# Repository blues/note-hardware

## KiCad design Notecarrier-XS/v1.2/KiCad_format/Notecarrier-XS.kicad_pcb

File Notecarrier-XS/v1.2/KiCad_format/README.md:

# Notecarrier-XS — KiCad format

This directory contains the design files for the Blues **Notecarrier-XS**
in **KiCad 9** format, ported from the internal Altium Designer sources
(project `100426_notecarrier-xs`, Byte Lab Grupa d.o.o. for Blues) and
validated against the shipped production BOM and the published v1.2
fabrication package — see
[`documentation/Porting-Notes.md`](documentation/Porting-Notes.md) and
[`validation/`](validation/).

> **⚠️ Disclaimer:** the exact Altium snapshot that produced the published
> v1.2 fabrication package was never captured in version control, so this
> port was made from the closest available source — the post-v1.2
> development state. It differs from the published v1.2 board in two
> reviewed, documented ways: the silkscreen reads **V1.3** (with legend text
> repositioned), and **R4** — a production-DNP 0R jumper for the optional
> GPS-power path — sits on the opposite board side. Copper, mask, paste and
> drill are otherwise exact against the published fab package, and the
> netlist matches the source design 57/57. Details in
> [`documentation/Porting-Notes.md`](documentation/Porting-Notes.md).
>
> Since publication the port has additionally been checked against the
> **released build's** pick-and-place file: all 44 placed parts match the
> shipped boards on side and rotation.
>
> The design house's October 2026 "Rev-11" snapshot turned out to be the
> **v1.1** board, not v1.2, so this disclaimer remains (the Notecarrier-X and
> -XM ports were regenerated from their Rev-11 snapshots and no longer carry
> one). See the Porting-Notes update.

## Contents

| Path | Description |
|---|---|
| `Notecarrier-XS.kicad_pro` / `.kicad_prl` | KiCad project |
| `Notecarrier-XS.kicad_sch` | Root schematic sheet |
| `Notecarrier-XS_IO-Connection.kicad_sch` | IO connection sheet |
| `Notecarrier-XS_Notecard-Connection.kicad_sch` | Notecard connection sheet |
| `Notecarrier-XS_Power.kicad_sch` | Power sheet |
| `Notecarrier-XS_Starnote-Connection.kicad_sch` | Starnote connection sheet |
| `Notecarrier-XS.kicad_pcb` | 2-layer board (zone fills preserved from the Altium import — do not refill) |
| `Notecarrier-XS.kicad_wks` | Drawing sheet (shared Blues template) |
| `Notecarrier-XS-altium-import.kicad_sym` / `.pretty/` | Project libraries captured during the import |
| `sym-lib-table` / `fp-lib-table` | Library tables |
| `documentation/` | Porting notes (incl. the source-fidelity disclaimer) and plotted PDFs |
| `manufacturing/Notecarrier-XS_RevA.zip` | KiCad-exported gerbers + drill |
| `validation/` | Validation-gate artifacts (ERC/DRC/BOM reports, per-layer gerber diffs, kicanvas renders) |

The schematic references the shared Blues symbol/footprint library via the
`BLUES_KICAD_LIB_DIR` path variable
([blues-kicad-lib](https://github.com/blues/blues-kicad-lib)), with all
symbols and footprints used by this design also embedded in the project
libraries above, so the project opens standalone.

## Provenance

Ported from Altium Designer sources with KiCad 9.0.9's importer and the
validation harness in
[`_Tools/kicad_validation/`](../../../_Tools/kicad_validation/). The original
Altium sources are internal and are not part of this repository; the
published v1.2 fabrication package (`../2200-914__2024-06-06.zip`), BOM
(`../BOM-3000-789-002.xlsx`) and drawings in the parent folder remain the
manufacturing ground truth for the shipped product.

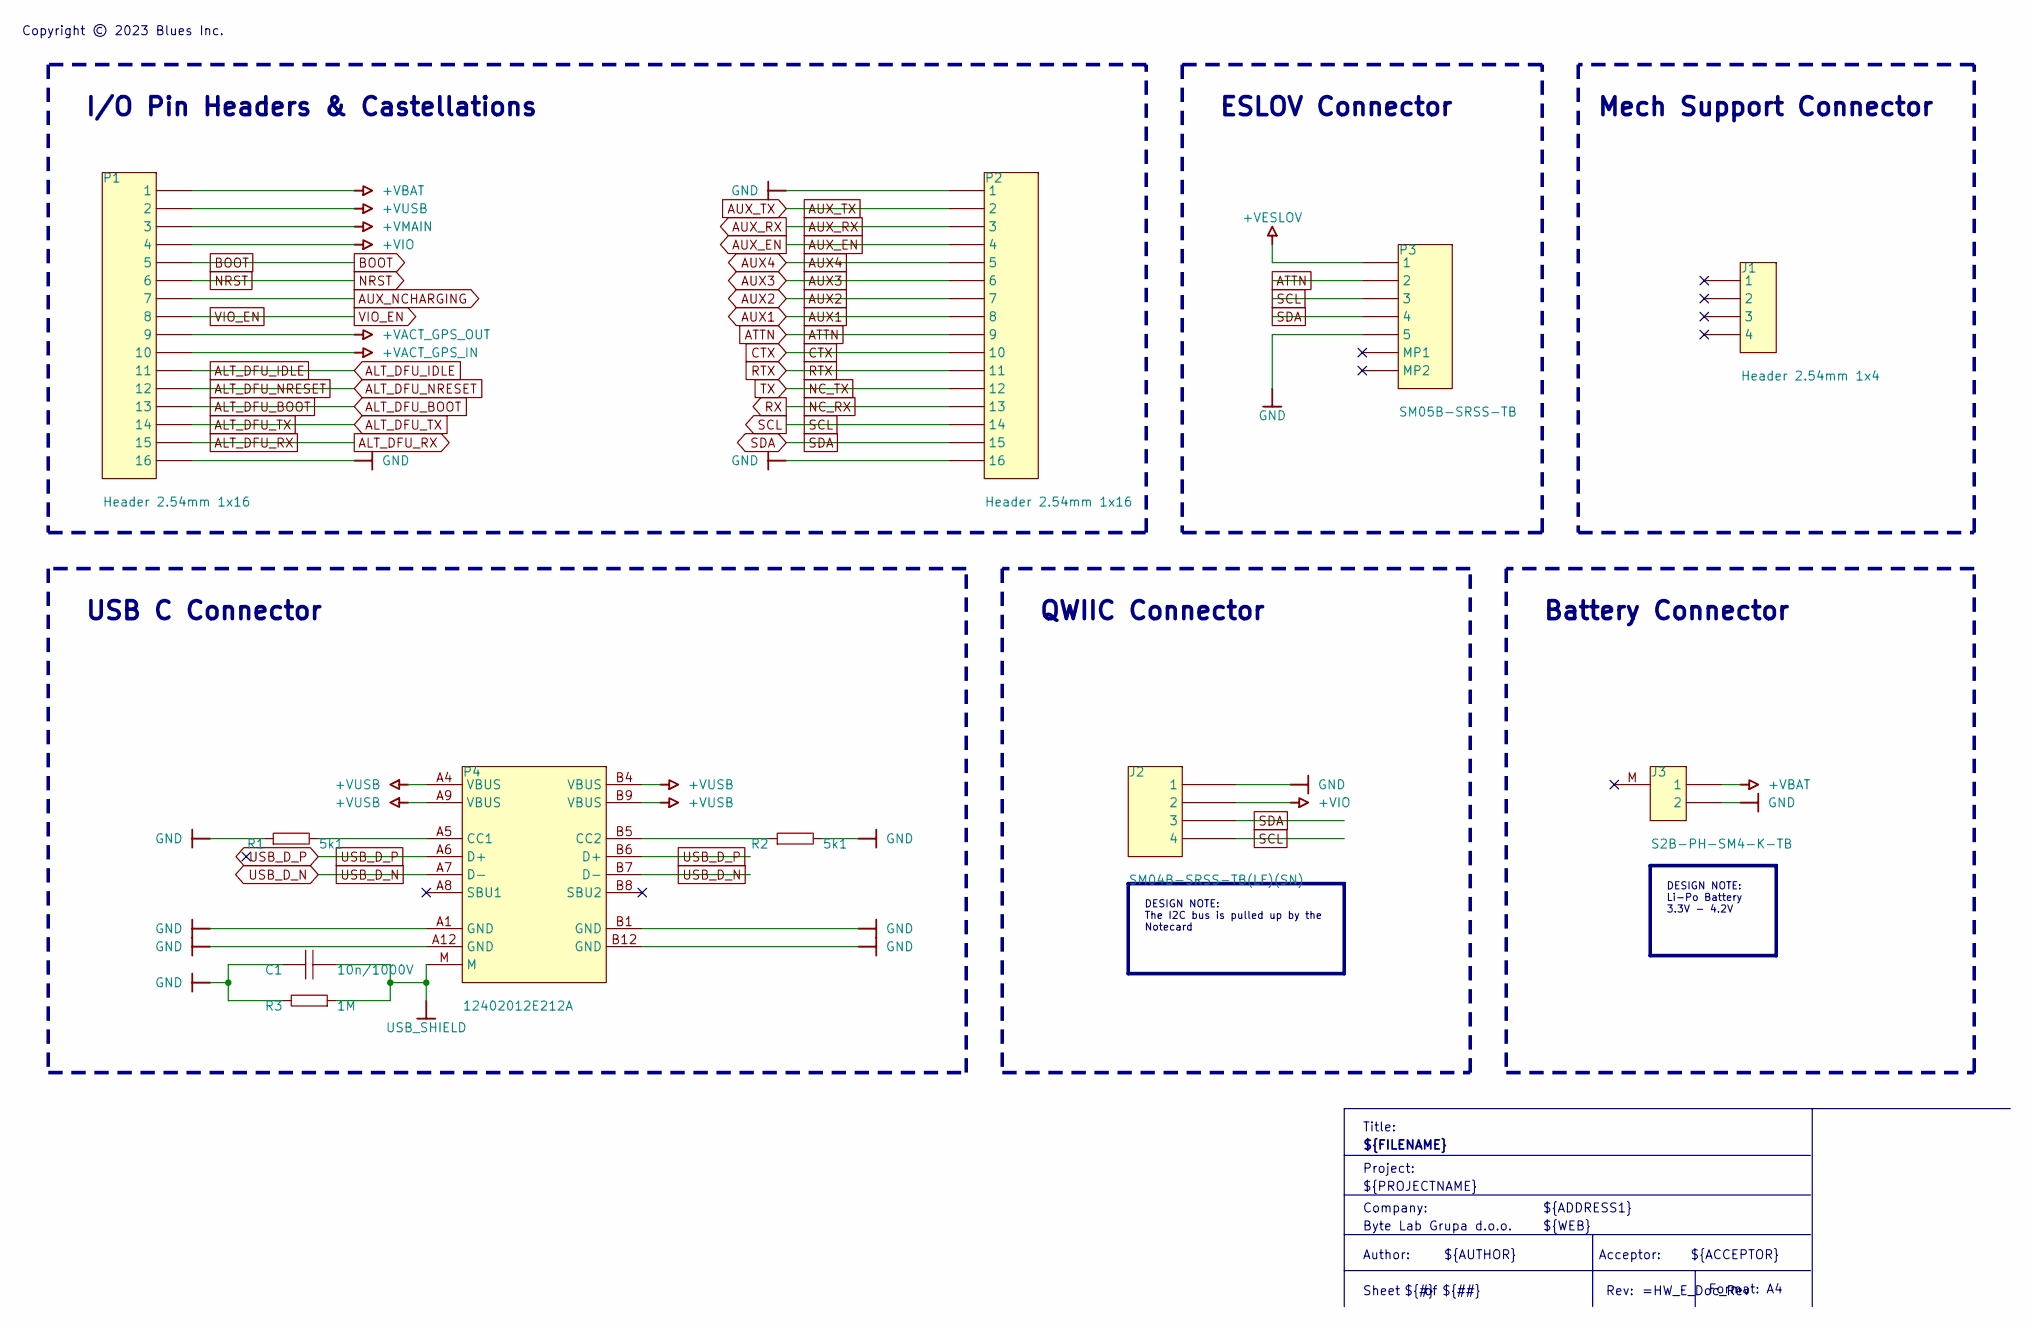
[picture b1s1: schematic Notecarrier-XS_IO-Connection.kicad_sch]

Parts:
C1: 10n/1000V; C-1206; MANUFACTURER PART NUMBER CS1206KKX7RCBB103
J1: Header 2.54mm 1x4; Header 2.54mm 1X4; MANUFACTURER PART NUMBER N/A
J2: SM04B-SRSS-TB(LF)(SN); JST SM04B-SRSS-TB; MANUFACTURER PART NUMBER SM04B-SRSS-TB(LF)(SN)
J3: S2B-PH-SM4-K-TB; Conn S2B-PH-SM4; MANUFACTURER PART NUMBER S2B-PH-SM4-K-TB(LF)(SN)
P1, P2: Header 2.54mm 1x16; Header 2.54mm 1X16; MANUFACTURER PART NUMBER N/A
P3: SM05B-SRSS-TB; Conn_SM05B-SRSS-TB; MANUFACTURER PART NUMBER SM05B-SRSS-TB
P4: 12402012E212A; CONN_12402012E212A; MANUFACTURER PART NUMBER 12402012E212A
R1, R2: 5k1; R-0402; MANUFACTURER PART NUMBER N/A
R3: 1M; R-1206; MANUFACTURER PART NUMBER N/A

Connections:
+VACT_GPS_IN: P1.10; also elsewhere on the board
+VACT_GPS_OUT: P1.9; also elsewhere on the board
+VBAT: J3.1, P1.1; also elsewhere on the board
+VESLOV: P3.1; also elsewhere on the board
+VIO: J2.2, P1.4; also elsewhere on the board
+VMAIN: P1.3; also elsewhere on the board
+VUSB: P1.2, P4.A4 (VBUS), P4.A9 (VBUS), P4.B4 (VBUS), P4.B9 (VBUS); also elsewhere on the board
ALT_DFU_BOOT: P1.13; also elsewhere on the board
ALT_DFU_IDLE: P1.11; also elsewhere on the board
ALT_DFU_NRESET: P1.12; also elsewhere on the board
ALT_DFU_RX: P1.15; also elsewhere on the board
ALT_DFU_TX: P1.14; also elsewhere on the board
ATTN: P2.9, P3.2; also elsewhere on the board
AUX1: P2.8; also elsewhere on the board
AUX2: P2.7; also elsewhere on the board
AUX3: P2.6; also elsewhere on the board
AUX4: P2.5; also elsewhere on the board
AUX_EN: P2.4; also elsewhere on the board
AUX_NCHARGING: P1.7; also elsewhere on the board
AUX_RX: P2.3; also elsewhere on the board
AUX_TX: P2.2; also elsewhere on the board
BOOT: P1.5; also elsewhere on the board
CTX: P2.10; also elsewhere on the board
GND: C1.2, J2.1, J3.2, P1.16, P2.1, P2.16, P3.5, P4.A1 (GND), P4.A12 (GND), P4.B1 (GND), P4.B12 (GND), R1.1, R2.2, R3.2; also elsewhere on the board
NC_RX: P2.13; also elsewhere on the board
NC_TX: P2.12; also elsewhere on the board
NRST: P1.6; also elsewhere on the board
unnamed: P4.A5 (CC1), R1.2
unnamed: P4.B5 (CC2), R2.1
RTX: P2.11; also elsewhere on the board
SCL: J2.4, P2.14, P3.3; also elsewhere on the board
SDA: J2.3, P2.15, P3.4; also elsewhere on the board
USB_D_N: P4.A7 (D-), P4.B7 (D-); also elsewhere on the board
USB_D_P: P4.A6 (D+), P4.B6 (D+); also elsewhere on the board
USB_SHIELD: C1.1, P4.M, R3.1
VIO_EN: P1.8; also elsewhere on the board

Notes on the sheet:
ESLOV Connector
${ACCEPTOR}
QWIIC Connector
Title:
Rev:
Sheet
Format: A4
Author:
I/O Pin Headers & Castellations
${ADDRESS1}
Acceptor:
${##}
${FILENAME}
Mech Support Connector
Company:
${REVISION}
${WEB}
${COMPANY}
Copyright © 2023 Blues Inc.
Battery Connector
USB C Connector
${#}
${AUTHOR}
${PROJECTNAME}
Project:
DESIGN NOTE: Li-Po Battery 3.3V - 4.2V
DESIGN NOTE: The I2C bus is pulled up by the Notecard

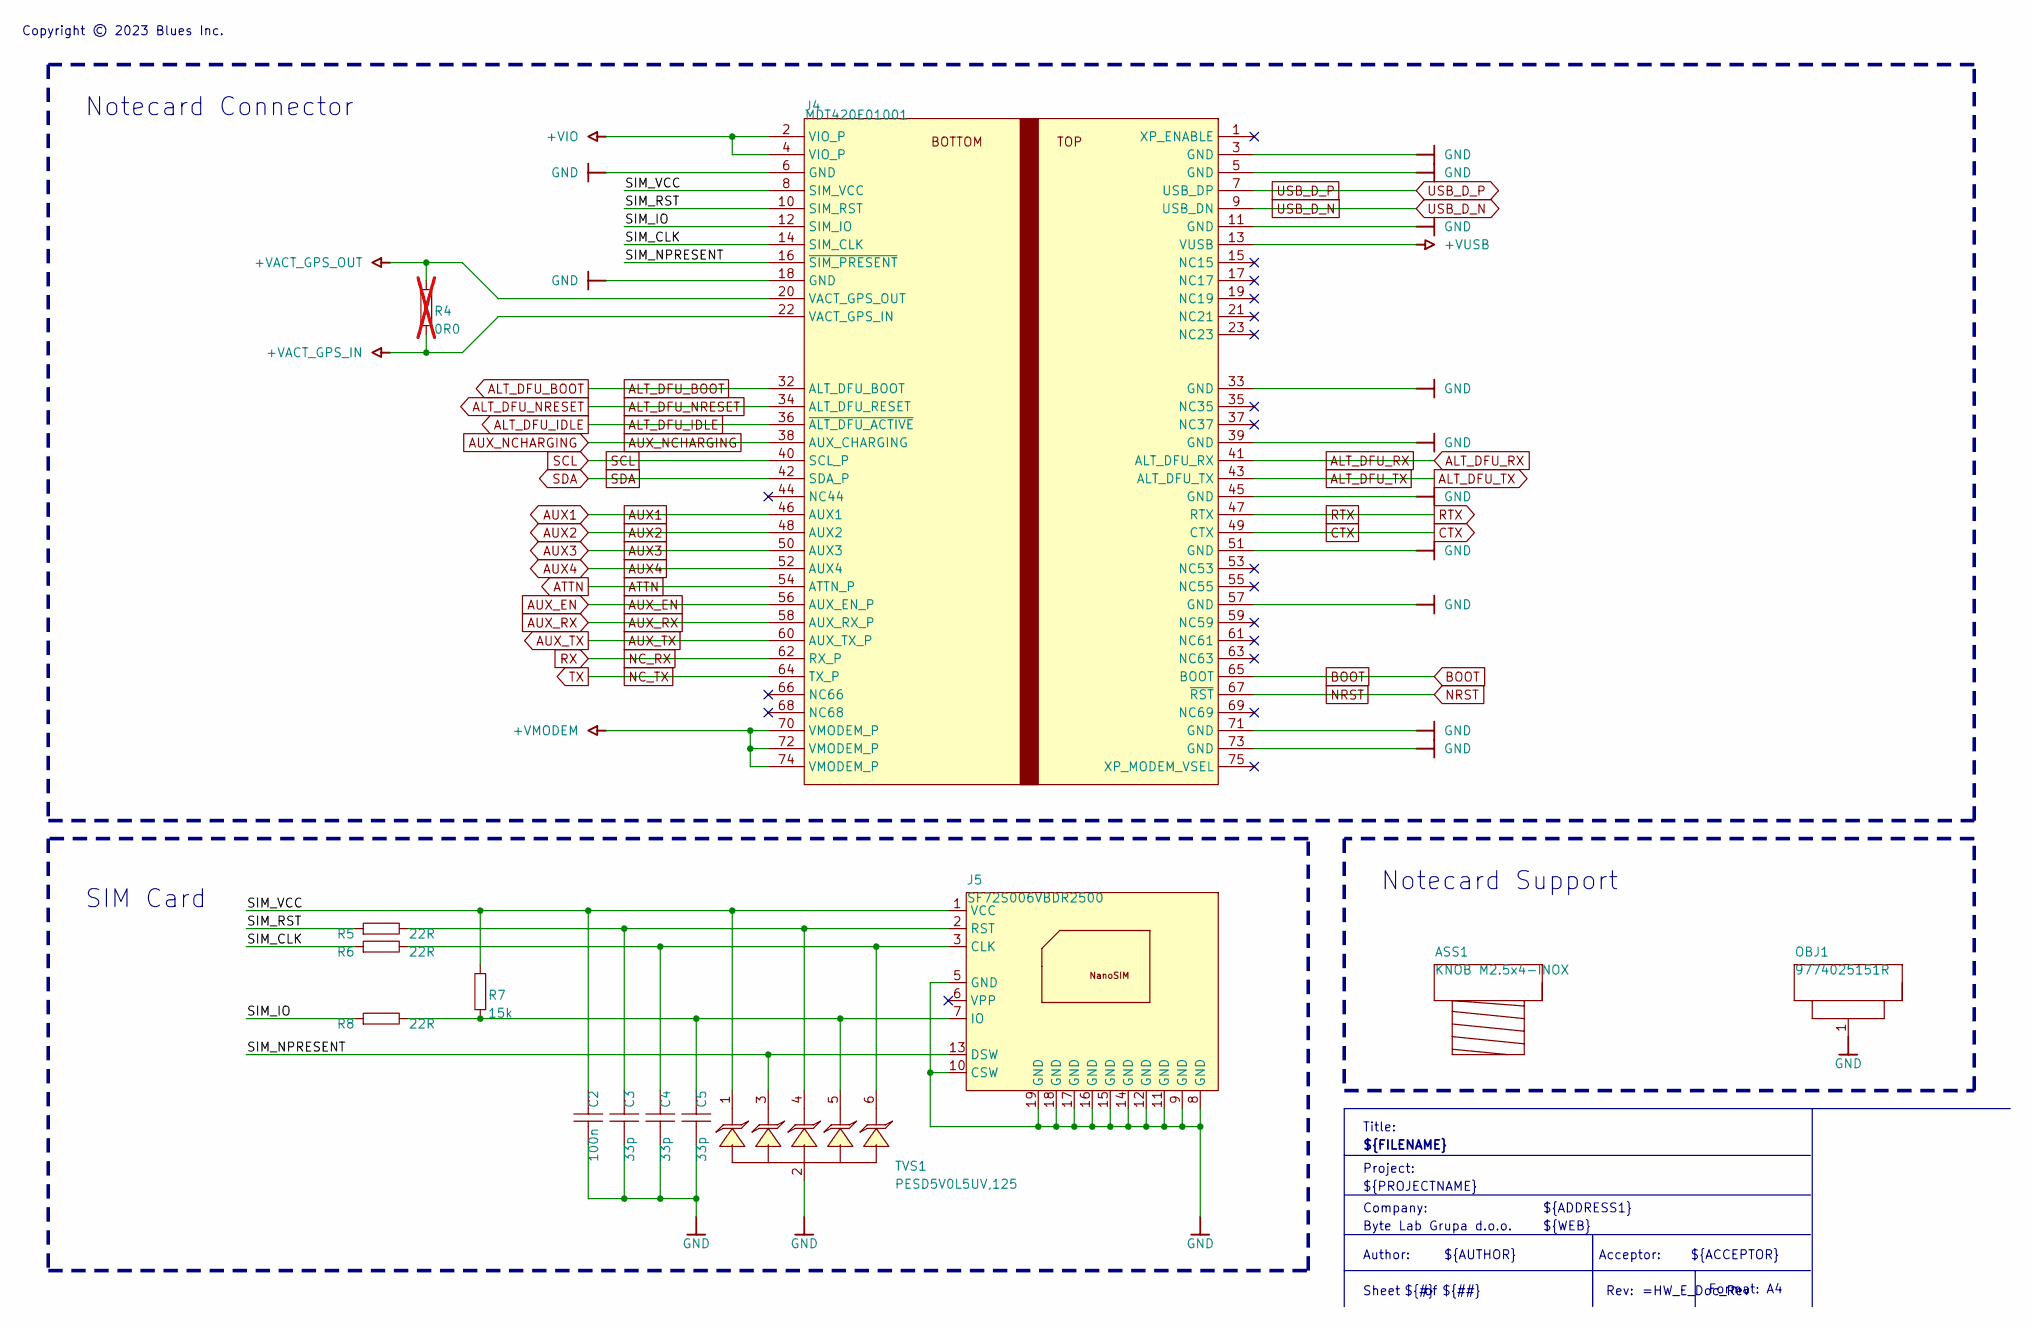
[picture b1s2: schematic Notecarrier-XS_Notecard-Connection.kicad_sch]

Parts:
ASS1: KNOB M2.5x4-INOX; MANUFACTURER PART NUMBER M2.5X4/D7985-A2
C2: 100n; C-0402; MANUFACTURER PART NUMBER N/A
C3, C4, C5: 33p; C-0402; MANUFACTURER PART NUMBER N/A
J4: MDT420E01001; J-75-0050-MOS-M2; MANUFACTURER PART NUMBER MDT420E03001
J5: SF72S006VBDR2500; J-NANOSIM-SF72S006VBA; MANUFACTURER PART NUMBER SF72S006VBDR2500
OBJ1: 9774025151R; DIST-WASMSIM0250; MANUFACTURER PART NUMBER 9774025151R
R4: 0R0; R-0603; MANUFACTURER PART NUMBER N/A; not fitted
R5, R6, R8: 22R; R-0402; MANUFACTURER PART NUMBER N/A
R7: 15k; R-0402; MANUFACTURER PART NUMBER N/A
TVS1: PESD5V0L5UV,125; SOT666; MANUFACTURER PART NUMBER PESD5V0L5UV,125

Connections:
+VACT_GPS_IN: J4.22 (VACT_GPS_IN), R4.1; also elsewhere on the board
+VACT_GPS_OUT: J4.20 (VACT_GPS_OUT), R4.2; also elsewhere on the board
+VIO: J4.2 (VIO_P), J4.4 (VIO_P); also elsewhere on the board
+VMODEM: J4.70 (VMODEM_P), J4.72 (VMODEM_P), J4.74 (VMODEM_P); also elsewhere on the board
+VUSB: J4.13 (VUSB); also elsewhere on the board
/Notecard Connection/SIM_CLK: J4.14 (SIM_CLK), R6.1
/Notecard Connection/SIM_IO: J4.12 (SIM_IO), R8.1
/Notecard Connection/SIM_NPRESENT: J4.16 (~SIM_PRESENT), J5.13 (DSW), TVS1.3 (C3)
/Notecard Connection/SIM_RST: J4.10 (SIM_RST), R5.1
/Notecard Connection/SIM_VCC: C2.2, J4.8 (SIM_VCC), J5.1 (VCC), R7.2, TVS1.1 (C1)
ALT_DFU_BOOT: J4.32 (ALT_DFU_BOOT); also elsewhere on the board
ALT_DFU_IDLE: J4.36 (~ALT_DFU_ACTIVE); also elsewhere on the board
ALT_DFU_NRESET: J4.34 (ALT_DFU_RESET); also elsewhere on the board
ALT_DFU_RX: J4.41 (ALT_DFU_RX); also elsewhere on the board
ALT_DFU_TX: J4.43 (ALT_DFU_TX); also elsewhere on the board
ATTN: J4.54 (ATTN_P); also elsewhere on the board
AUX1: J4.46 (AUX1); also elsewhere on the board
AUX2: J4.48 (AUX2); also elsewhere on the board
AUX3: J4.50 (AUX3); also elsewhere on the board
AUX4: J4.52 (AUX4); also elsewhere on the board
AUX_EN: J4.56 (AUX_EN_P); also elsewhere on the board
AUX_NCHARGING: J4.38 (AUX_CHARGING); also elsewhere on the board
AUX_RX: J4.58 (AUX_RX_P); also elsewhere on the board
AUX_TX: J4.60 (AUX_TX_P); also elsewhere on the board
BOOT: J4.65 (BOOT); also elsewhere on the board
CTX: J4.49 (CTX); also elsewhere on the board
GND: C2.1, C3.1, C4.1, C5.1, J4.3 (GND), J4.5 (GND), J4.6 (GND), J4.11 (GND), J4.18 (GND), J4.33 (GND), J4.39 (GND), J4.45 (GND), J4.51 (GND), J4.57 (GND), J4.71 (GND), J4.73 (GND), J5.5 (GND), J5.8 (GND), J5.9 (GND), J5.10 (CSW), J5.11 (GND), J5.12 (GND), J5.14 (GND), J5.15 (GND), J5.16 (GND), J5.17 (GND), J5.18 (GND), J5.19 (GND), OBJ1.1, TVS1.2 (A2); also elsewhere on the board
NC_RX: J4.62 (RX_P); also elsewhere on the board
NC_TX: J4.64 (TX_P); also elsewhere on the board
NRST: J4.67 (~RST); also elsewhere on the board
unnamed: C4.2, J5.3 (CLK), R6.2, TVS1.6 (C6)
unnamed: C5.2, J5.7 (IO), R7.1, R8.2, TVS1.5 (A5)
unnamed: C3.2, J5.2 (RST), R5.2, TVS1.4 (C4)
RTX: J4.47 (RTX); also elsewhere on the board
SCL: J4.40 (SCL_P); also elsewhere on the board
SDA: J4.42 (SDA_P); also elsewhere on the board
USB_D_N: J4.9 (USB_DN); also elsewhere on the board
USB_D_P: J4.7 (USB_DP); also elsewhere on the board

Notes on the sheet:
Notecard Connector
${ADDRESS1}
Rev:
Company:
Format: A4
${WEB}
Copyright © 2023 Blues Inc.
Author:
${##}
Sheet
Title:
Project:
${COMPANY}
Acceptor:
${ACCEPTOR}
${FILENAME}
${#}
Notecard Support
${REVISION}
${PROJECTNAME}
SIM Card
${AUTHOR}

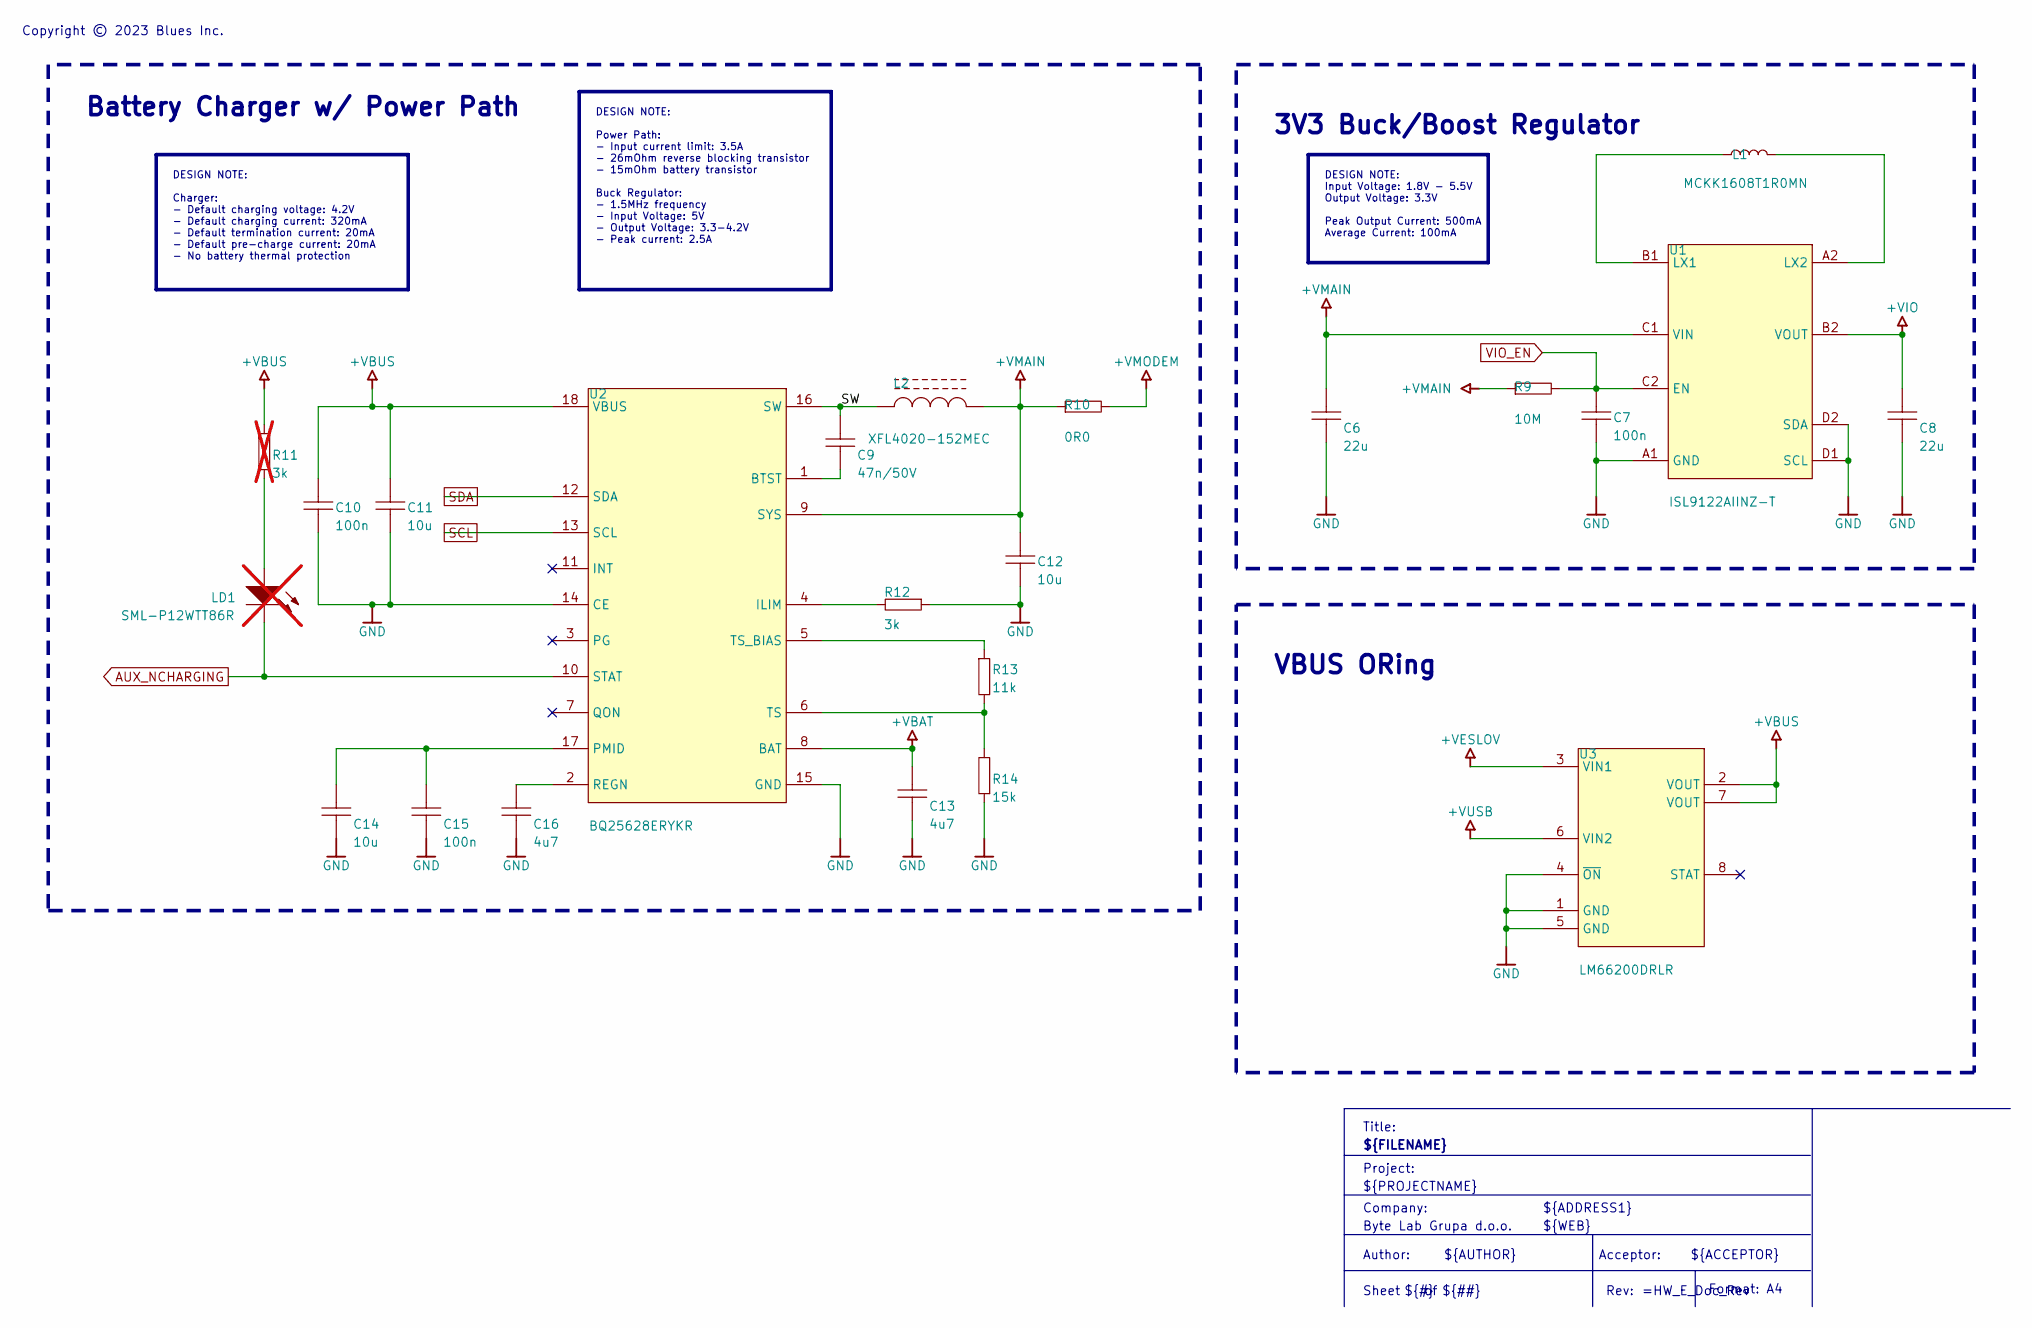
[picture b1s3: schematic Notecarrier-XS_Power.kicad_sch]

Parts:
C6, C8: 22u; C-0805; MANUFACTURER PART NUMBER N/A
C7, C10, C15: 100n; C-0402; MANUFACTURER PART NUMBER N/A
C9: 47n/50V; C-0402; MANUFACTURER PART NUMBER N/A
C11, C12: 10u; C-1206; MANUFACTURER PART NUMBER N/A
C13, C16: 4u7; C-0603; MANUFACTURER PART NUMBER N/A
C14: 10u; C-0805; MANUFACTURER PART NUMBER GRM21BR61E106MA73L
L1: MCKK1608T1R0MN; L-0603; MANUFACTURER PART NUMBER MCKK1608T1R0MN
L2: XFL4020-152MEC; IND_XFL4020; MANUFACTURER PART NUMBER XFL4020-152MEC
LD1: SML-P12WTT86R; LED-0402; MANUFACTURER PART NUMBER SML-P12WTT86R; not fitted
R9: 10M; R-0402; MANUFACTURER PART NUMBER N/A
R10: 0R0; R-0603; MANUFACTURER PART NUMBER N/A
R11: 3k; R-0402; MANUFACTURER PART NUMBER N/A; not fitted
R12: 3k; R-0402; MANUFACTURER PART NUMBER N/A
R13: 11k; R-0402; MANUFACTURER PART NUMBER N/A
R14: 15k; R-0402; MANUFACTURER PART NUMBER N/A
U1: ISL9122AIINZ-T; BGA8N40P2X4_180x100x50; MANUFACTURER PART NUMBER ISL9122AIINZ-T
U2: BQ25628ERYKR; QFN40P300X150X80-18N; MANUFACTURER PART NUMBER BQ25628ERYKR
U3: LM66200DRLR; SOT-583; MANUFACTURER PART NUMBER LM66200DRLR

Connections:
+VBAT: C13.2, U2.8 (BAT); also elsewhere on the board
+VBUS: C10.1, C11.1, R11.2, U2.18 (VBUS), U3.2 (VOUT), U3.7 (VOUT)
+VESLOV: U3.3 (VIN1); also elsewhere on the board
+VIO: C8.2, U1.B2 (VOUT); also elsewhere on the board
+VMAIN: C6.2, C12.1, L2.2, R9.1, R10.1, U1.C1 (VIN), U2.9 (SYS); also elsewhere on the board
+VMODEM: R10.2; also elsewhere on the board
+VUSB: U3.6 (VIN2); also elsewhere on the board
/Power/SW: C9.2, L2.1, U2.16 (SW)
AUX_NCHARGING: LD1.2 (K), U2.10 (STAT); also elsewhere on the board
GND: C6.1, C7.2, C8.1, C10.2, C11.2, C12.2, C13.1, C14.1, C15.1, C16.1, R12.1, R14.1, U1.A1 (GND), U1.D1 (SCL), U1.D2 (SDA), U2.14 (CE), U2.15 (GND), U3.1 (GND), U3.4 (~ON), U3.5 (GND); also elsewhere on the board
unnamed: LD1.1 (A), R11.1
unnamed: L1.1, U1.B1 (LX1)
unnamed: L1.2, U1.A2 (LX2)
unnamed: C9.1, U2.1 (BTST)
unnamed: R12.2, U2.4 (ILIM)
unnamed: C14.2, C15.2, U2.17 (PMID)
unnamed: C16.2, U2.2 (REGN)
unnamed: R13.2, R14.2, U2.6 (TS)
unnamed: R13.1, U2.5 (TS_BIAS)
SCL: U2.13 (SCL); also elsewhere on the board
SDA: U2.12 (SDA); also elsewhere on the board
VIO_EN: C7.1, R9.2, U1.C2 (EN); also elsewhere on the board

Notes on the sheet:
Copyright © 2023 Blues Inc.
Company:
${ADDRESS1}
${REVISION}
Acceptor:
Rev:
${##}
${PROJECTNAME}
${#}
Format: A4
Project:
${COMPANY}
${ACCEPTOR}
${WEB}
${FILENAME}
Sheet
VBUS ORing
3V3 Buck/Boost Regulator
Battery Charger w/ Power Path
Author:
${AUTHOR}
Title:
DESIGN NOTE: Input Voltage: 1.8V - 5.5V Output Voltage: 3.3V Peak Output Current: 500mA Average Current: 100mA
DESIGN NOTE: Charger: - Default charging voltage: 4.2V - Default charging current: 320mA - Default termination current: 20mA - Default pre-charge current: 20mA - No battery thermal protection
DESIGN NOTE: Power Path: - Input current limit: 3.5A - 26mOhm reverse blocking transistor - 15mOhm battery transistor Buck Regulator: - 1.5MHz frequency - Input Voltage: 5V - Output Voltage: 3.3-4.2V - Peak current: 2.5A

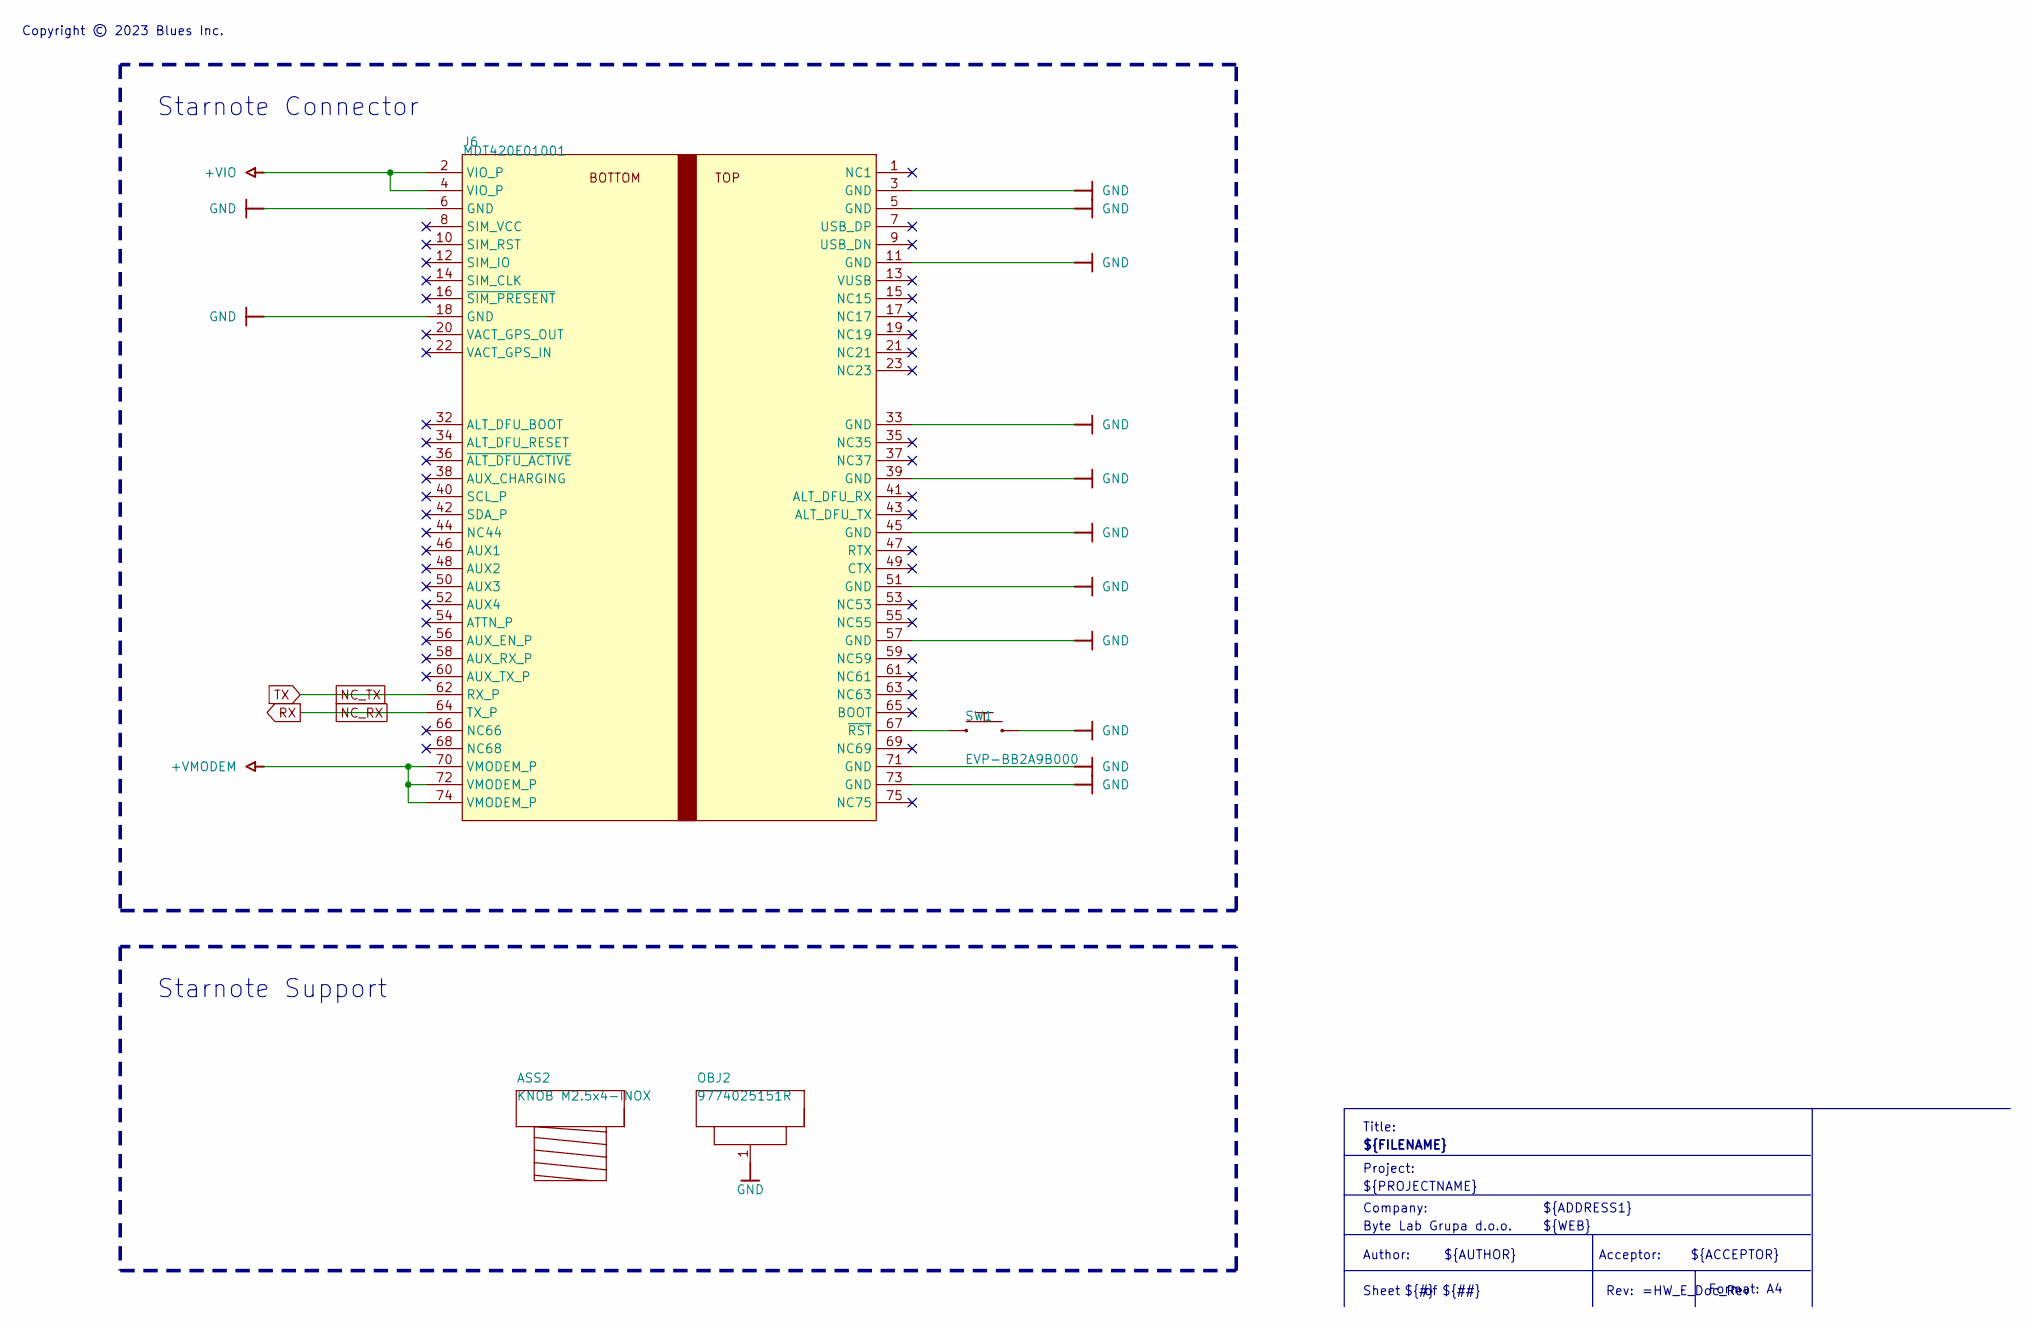
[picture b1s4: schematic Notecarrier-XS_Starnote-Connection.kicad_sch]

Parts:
ASS2: KNOB M2.5x4-INOX; MANUFACTURER PART NUMBER M2.5X4/D7985-A2
J6: MDT420E01001; J-75-0050-MOS-M2; MANUFACTURER PART NUMBER MDT420E03001
OBJ2: 9774025151R; DIST-WASMSIM0250; MANUFACTURER PART NUMBER 9774025151R
SW1: EVP-BB2A9B000; SW_EVP-BB2A9B000; MANUFACTURER PART NUMBER EVP-BB2A9B000

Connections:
+VIO: J6.2 (VIO_P), J6.4 (VIO_P); also elsewhere on the board
+VMODEM: J6.70 (VMODEM_P), J6.72 (VMODEM_P), J6.74 (VMODEM_P); also elsewhere on the board
GND: J6.3 (GND), J6.5 (GND), J6.6 (GND), J6.11 (GND), J6.18 (GND), J6.33 (GND), J6.39 (GND), J6.45 (GND), J6.51 (GND), J6.57 (GND), J6.71 (GND), J6.73 (GND), OBJ2.1, SW1.2 (B); also elsewhere on the board
NC_RX: J6.64 (TX_P); also elsewhere on the board
NC_TX: J6.62 (RX_P); also elsewhere on the board
unnamed: J6.67 (~RST), SW1.1 (A)

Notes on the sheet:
${COMPANY}
Rev:
${AUTHOR}
Sheet
Acceptor:
Format: A4
${REVISION}
${#}
Copyright © 2023 Blues Inc.
Author:
Starnote Support
${##}
Title:
Company:
${ACCEPTOR}
Project:
${ADDRESS1}
Starnote Connector
${FILENAME}
${WEB}
${PROJECTNAME}

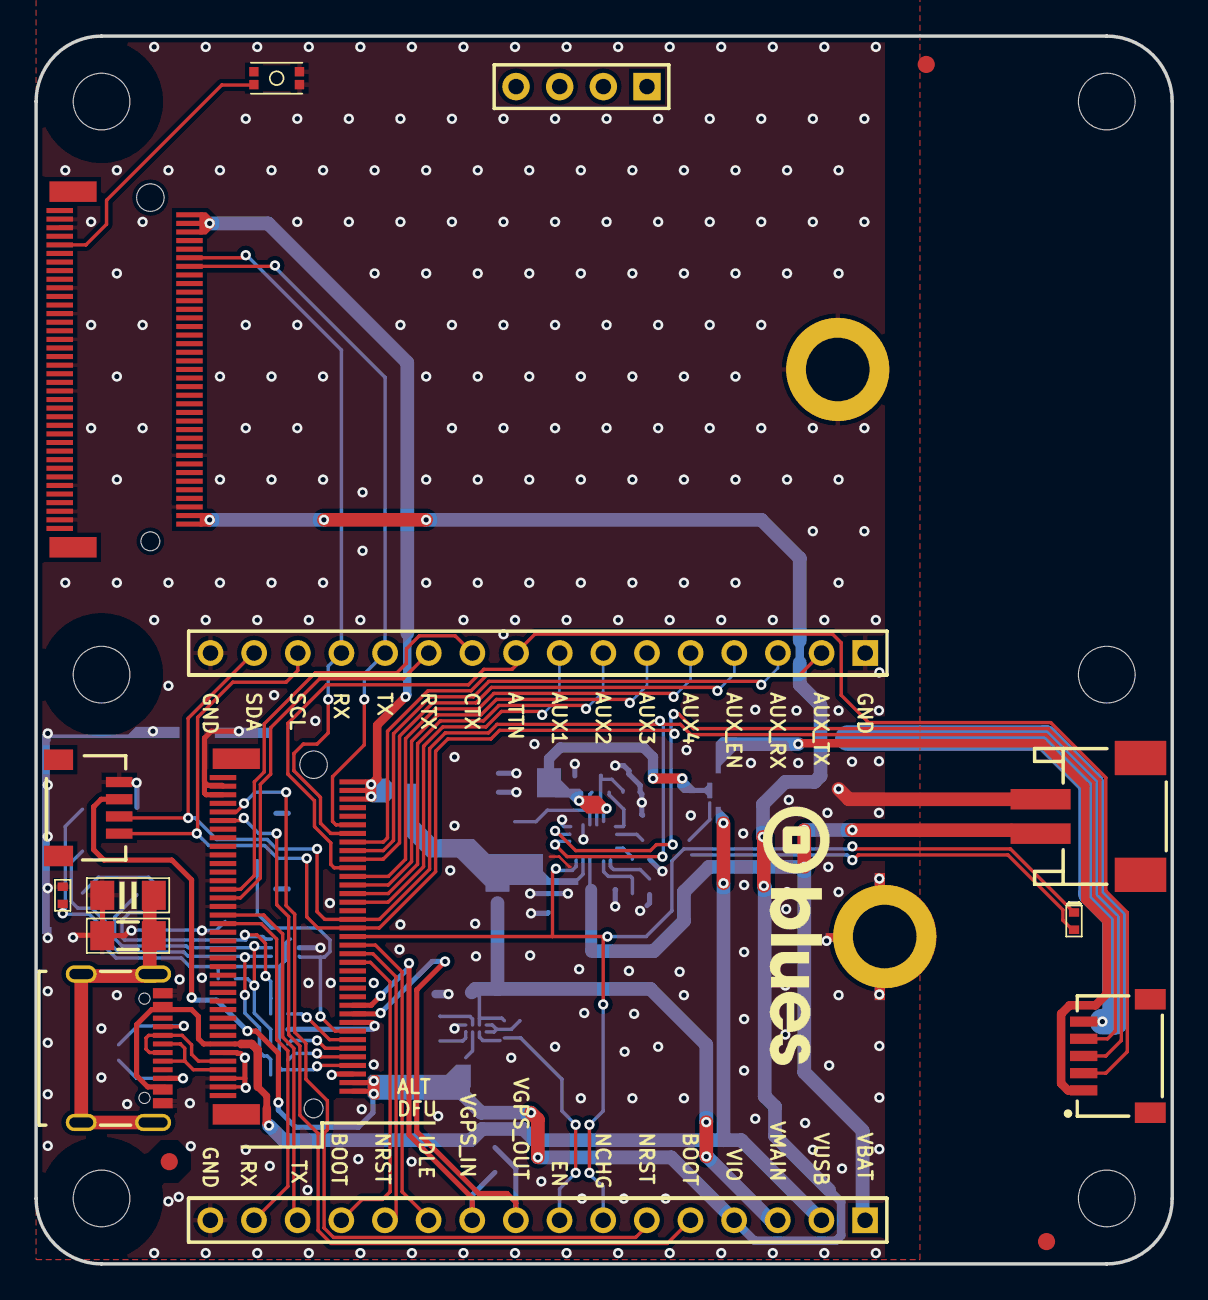
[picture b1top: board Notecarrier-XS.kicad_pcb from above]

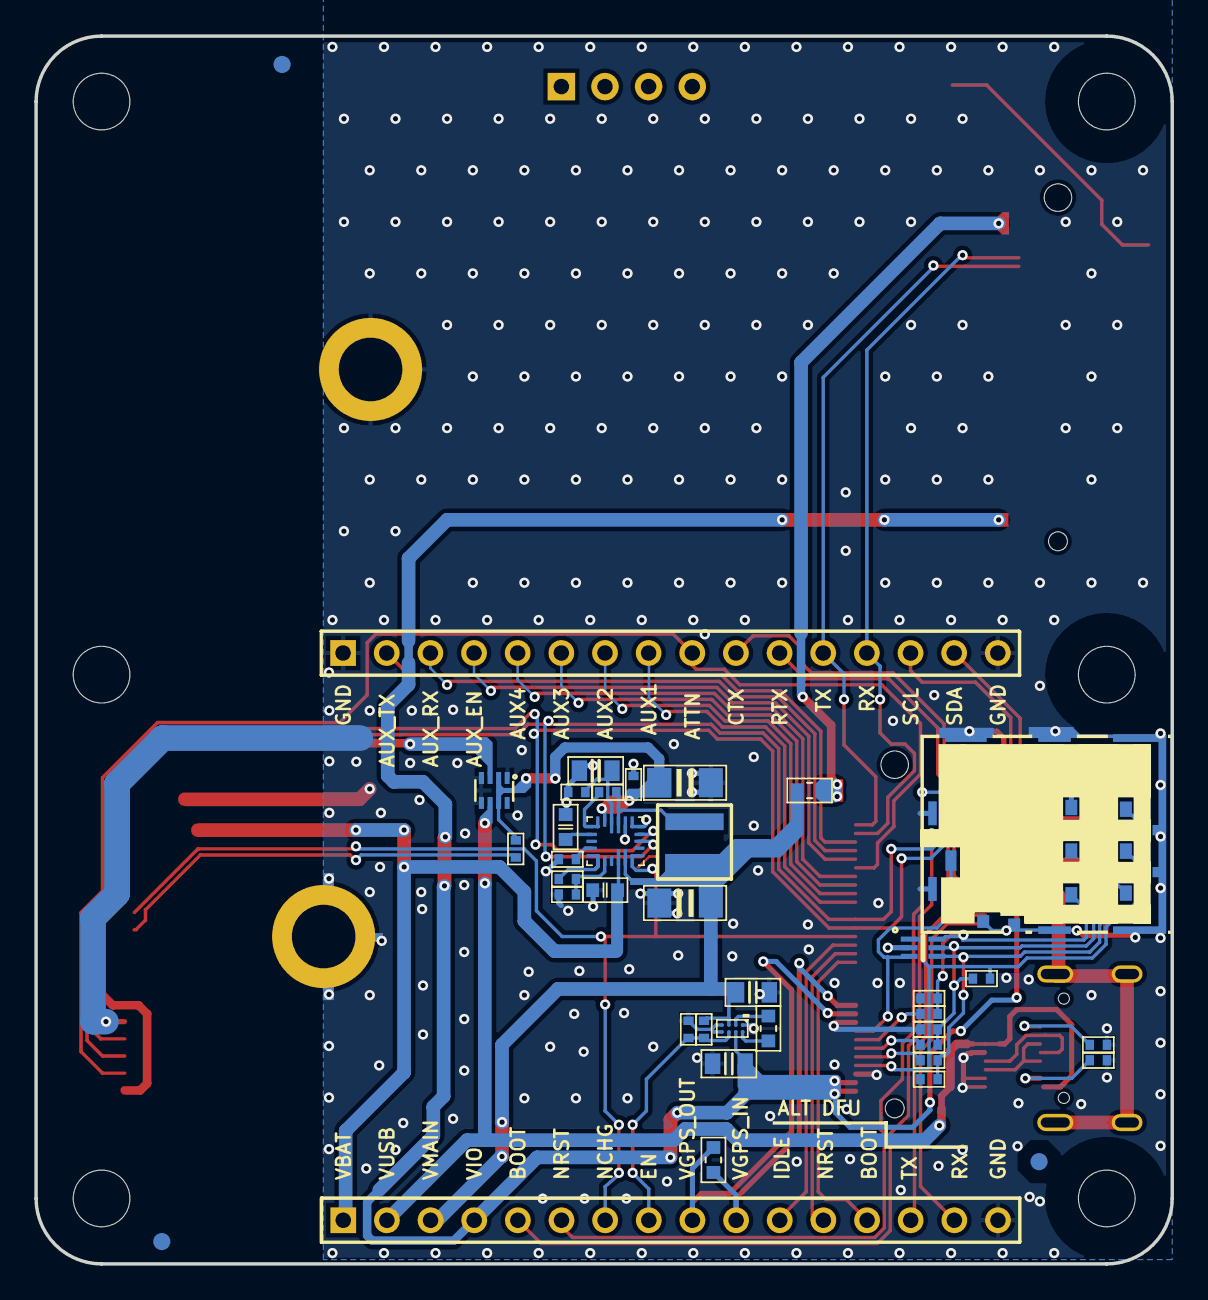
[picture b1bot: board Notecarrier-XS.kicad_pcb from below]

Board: 2 copper layers, 66.1 x 71.5 mm, 56 parts (37 on the bottom side), 57 nets.

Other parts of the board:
FD1, FD2, FD3, FD4, FD5, FD6: Fiducial mark; Fiducial mark 1mm

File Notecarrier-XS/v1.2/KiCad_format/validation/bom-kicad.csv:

"Reference","Value","MPN","DNP"
"ASS1","KNOB M2.5x4-INOX","6000-168",""
"ASS2","KNOB M2.5x4-INOX","6000-168",""
"C1","10n/1000V","2007-449",""
"C2","100n","2000-908",""
"C3","33p","2001-377",""
"C4","33p","2001-377",""
"C5","33p","2001-377",""
"C6","22u","2006-222",""
"C7","100n","2000-908",""
"C8","22u","2006-222",""
"C9","47n/50V","2003-965",""
"C10","100n","2000-908",""
"C11","10u","2000-447",""
"C12","10u","2000-447",""
"C13","4u7","2003-721",""
"C14","10u","2004-293",""
"C15","100n","2004-296",""
"C16","4u7","2003-721",""
"J1","Header 2.54mm 1x4","2001-524",""
"J2","SM04B-SRSS-TB(LF)(SN)","2002-058",""
"J3","S2B-PH-SM4-K-TB","2007-662",""
"J4","MDT420E01001","2007-460",""
"J5","SF72S006VBDR2500","2007-458",""
"J6","MDT420E01001","2007-460",""
"L1","MCKK1608T1R0MN","2003-989",""
"L2","XFL4020-152MEC","2006-846",""
"LD1","SML-P12WTT86R","2007-660","DNP"
"OBJ1","9774025151R","6020-113",""
"OBJ2","9774025151R","6020-113",""
"P1","Header 2.54mm 1x16","2001-478",""
"P2","Header 2.54mm 1x16","2001-478",""
"P3","SM05B-SRSS-TB","2008-432",""
"P4","12402012E212A","2008-437",""
"R1","5k1","2004-098",""
"R2","5k1","2004-098",""
"R3","1M","2001-438",""
"R4","0R0","2000-723","DNP"
"R5","22R","2001-170",""
"R6","22R","2001-170",""
"R7","15k","2001-157",""
"R8","22R","2001-170",""
"R9","10M","2002-832",""
"R10","0R0","2000-723",""
"R11","3k","2001-570","DNP"
"R12","3k","2001-570",""
"R13","11k","2004-237",""
"R14","15k","2001-157",""
"SW1","EVP-BB2A9B000","2007-124",""
"TVS1","PESD5V0L5UV,125","2007-452",""
"U1","ISL9122AIINZ-T","2007-147",""
"U2","BQ25628ERYKR","2008-206",""
"U3","LM66200DRLR","2007-318",""
